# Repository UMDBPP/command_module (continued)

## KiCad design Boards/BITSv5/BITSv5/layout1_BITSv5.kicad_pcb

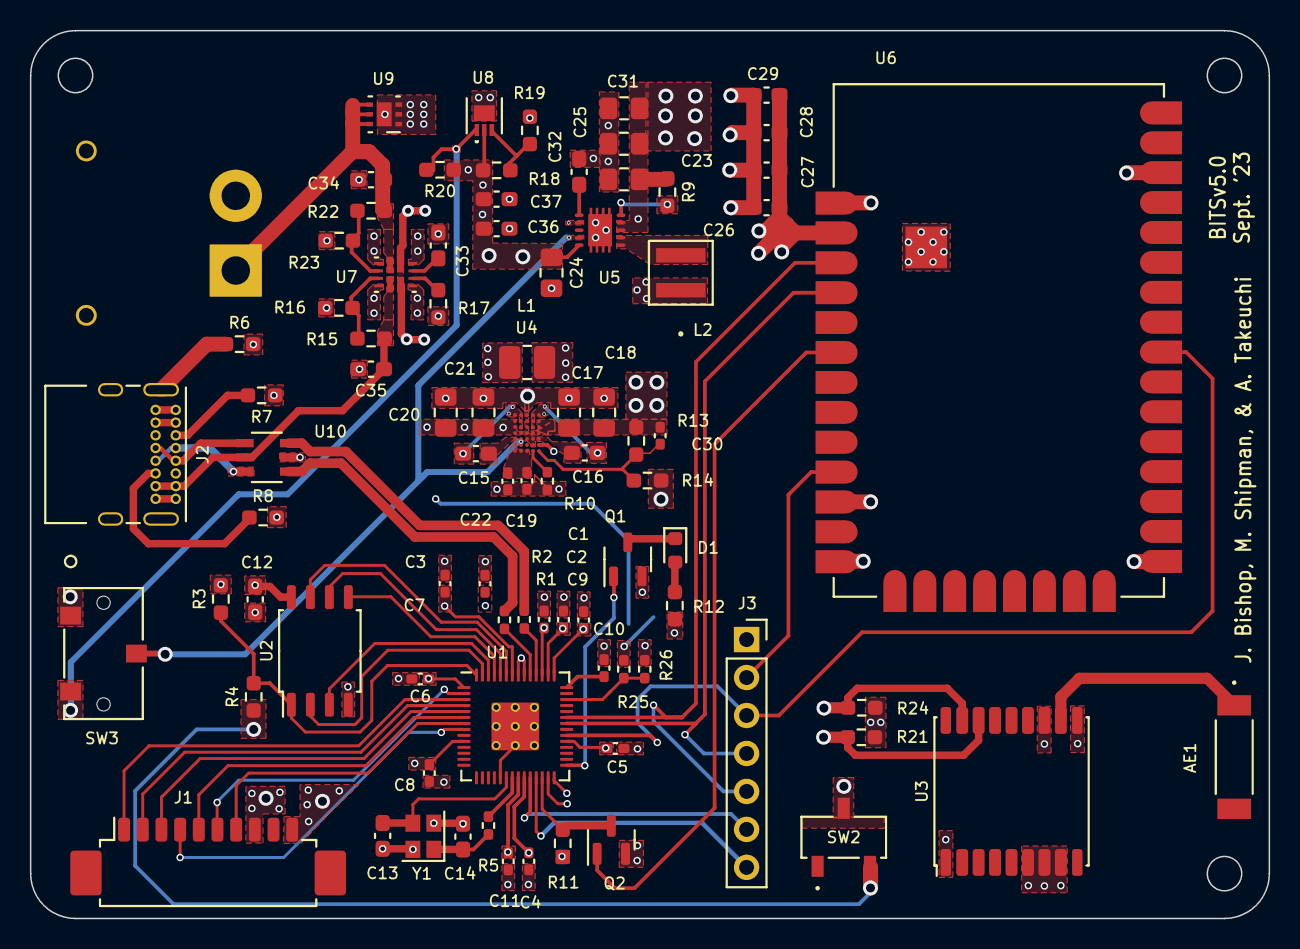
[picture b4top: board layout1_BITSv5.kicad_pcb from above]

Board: 4 copper layers, 82.9 x 59.4 mm, 86 parts (1 on the bottom side), 65 nets.

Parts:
AE1: Antenna; ANT_1575AT_JOT-M
BT1: 1S1P LiPo; AMASS_XT30PW-M_1x02_P2.50mm_Horizontal
C1, C2: 1uF; C_0402_1005Metric_Pad0.74x0.62mm_HandSolder
C3, C4, C5, C6, C7, C8, C9, C10, C11: 100nF; C_0402_1005Metric_Pad0.74x0.62mm_HandSolder
C12, C28: 100nF; C_0603_1608Metric_Pad1.08x0.95mm_HandSolder
C13, C14: 10pF; C_0603_1608Metric_Pad1.08x0.95mm_HandSolder
C15, C16: 220nF; C_0603_1608Metric_Pad1.08x0.95mm_HandSolder
C17, C18, C23, C24, C25, C31: 22uF; C_0805_2012Metric_Pad1.18x1.45mm_HandSolder
C19: 470nF; C_0402_1005Metric_Pad0.74x0.62mm_HandSolder
C20, C21: 10uF; C_0805_2012Metric_Pad1.18x1.45mm_HandSolder
C22: 2.2uF; C_0402_1005Metric_Pad0.74x0.62mm_HandSolder
C26: 8.2pF; C_0603_1608Metric_Pad1.08x0.95mm_HandSolder
C27: 47pF; C_0603_1608Metric_Pad1.08x0.95mm_HandSolder
C29, C34, C35: 10uF; C_0603_1608Metric_Pad1.08x0.95mm_HandSolder
C30: 10pF; C_0402_1005Metric_Pad0.74x0.62mm_HandSolder
C32, C33: 10nF; C_0603_1608Metric_Pad1.08x0.95mm_HandSolder
C36, C37: 1uF; C_0603_1608Metric_Pad1.08x0.95mm_HandSolder
D1: LED; LED_0603_1608Metric
J1: Conn_01x10_Pin; Molex_PicoBlade_53261-1071_1x10-1MP_P1.25mm_Horizontal
J2: USB_C_Receptacle_USB2.0; USB_C_Receptacle_GCT_USB4085
J3: Conn_01x07; PinSocket_1x07_P2.54mm_Vertical
L1: 1uH; L_1008_2520Metric_Pad1.43x2.20mm_HandSolder
L2: 1uH; IND_XAL4020_4X4_COC-M
Q1: Q_NMOS_GSD; SOT-23-3
Q2: Q_PMOS_GSD; SOT-23
R1, R2: 27Ω; R_0402_1005Metric_Pad0.72x0.64mm_HandSolder
R3, R11, R21, R24: 10K; R_0603_1608Metric_Pad0.98x0.95mm_HandSolder
R4: 1K; R_0603_1608Metric_Pad0.98x0.95mm_HandSolder
R5: 1K; R_0402_1005Metric_Pad0.72x0.64mm_HandSolder
R6, R9: 1M; R_0603_1608Metric_Pad0.98x0.95mm_HandSolder
R7, R8: 5.1K; R_0603_1608Metric_Pad0.98x0.95mm_HandSolder
R10: 48.7K; R_0402_1005Metric_Pad0.72x0.64mm_HandSolder
R12: 470; R_0603_1608Metric_Pad0.98x0.95mm_HandSolder
R13: 178K; R_0603_1608Metric_Pad0.98x0.95mm_HandSolder
R14: 20K; R_0603_1608Metric_Pad0.98x0.95mm_HandSolder
R15, R22: 23.7K; R_0603_1608Metric_Pad0.98x0.95mm_HandSolder
R16, R23: 5K; R_0603_1608Metric_Pad0.98x0.95mm_HandSolder
R17: 51.1K; R_0603_1608Metric_Pad0.98x0.95mm_HandSolder
R18: 1.05M; R_0603_1608Metric_Pad0.98x0.95mm_HandSolder
R19: 154K; R_0603_1608Metric_Pad0.98x0.95mm_HandSolder
R20: 510K; R_0603_1608Metric_Pad0.98x0.95mm_HandSolder
R25: 15K; R_0402_1005Metric_Pad0.72x0.64mm_HandSolder
R26: 5K; R_0402_1005Metric_Pad0.72x0.64mm_HandSolder
SW2: CAS-120TB_NDC-M
SW3: SLIDE; CL-SB-12B-01_NDC
U1: MCU_RaspberryPi_RP2040_RP2040; RP2040-QFN-56
U2: W25Q128JVS; SOIC-8_5.23x5.23mm_P1.27mm
U3: MAX-M10S; ublox_MAX
U4: MAX77857; MAX77857-35WLP
U5: TPS61232DRCR; TPS61232
U6: XBee_SMT; XCVR_XBP9X-DMUS-001
U7: TPS2121RUXR; TPS2121
U8: LT6703CDC-3; DFN-3_DC_LIT
U9: TVS1800DRVR; TVS1800
U10: USBLC6-2SC6; SOT23-6L_STM-M
Y1: 12MHz; Crystal_SMD_2520-4Pin_2.5x2.0mm

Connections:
+1V1: C1.1, C3.1, C4.1, U1.23 (DVDD), U1.45 (VREG_VOUT), U1.50 (DVDD)
+3V3: C2.1, C5.1, C6.1, C7.1, C8.1, C9.1, C10.1, C11.1, C12.1, C17.1, C18.1, C26.1, C27.1, C28.1, C29.1, C30.1, R3.2, R11.1, R12.1, R13.1, R21.1, R24.1, U1.1 (IOVDD), U1.10 (IOVDD), U1.22 (IOVDD), U1.33 (IOVDD), U1.42 (IOVDD), U1.43 (ADC_AVDD), U1.44 (VREG_IN), U1.48 (USB_VDD), U1.49 (IOVDD), U2.8 (VCC), U3.6 (V_BCKP), U3.7 (VCC_IO), U3.8 (VCC), U4.D4 (OUT), U4.E4 (OUT), U4.E5 (OUT), U4.E6 (OUT), U6.2 (VCC)
+5V: C23.1, C25.1, C31.1, J1.8, R9.1, U5.3 (VOUT), U5.4 (VOUT), U5.7 (FB)
+BATT: BT1.1 (+), C34.1, R22.1, R25.1, U7.2 (IN2), U9.4 (IN), U9.5 (IN), U9.6 (IN)
/GPS_SCL: R24.2, U1.28 (GPIO17), U3.17 (SCL)
/GPS_SDA: R21.2, U1.27 (GPIO16), U3.16 (SDA)
/IRIDIUM_CTS: J1.2, U1.4 (GPIO2)
/IRIDIUM_NETAV: J1.4, U1.8 (GPIO6)
/IRIDIUM_ON/OFF: J1.7, U1.7 (GPIO5)
/IRIDIUM_RING: J1.5, U1.6 (GPIO4)
/IRIDIUM_RTS: J1.3, U1.5 (GPIO3)
/IRIDIUM_RXD: J1.1, U1.3 (GPIO1)
/IRIDIUM_TXD: J1.6, U1.2 (GPIO0)
/LED: Q1.1 (G), U1.29 (GPIO18)
/LVC_CUTOFF: SW3.2 (B), U4.B2 (EN), U4.B3 (EN), U5.9 (EN)
/QSPI_SCLK: U1.52 (QSPI_SCLK), U2.6 (CLK)
/QSPI_SD0: U1.53 (QSPI_SD0), U2.5 (DI(IO0))
/QSPI_SD1: U1.55 (QSPI_SD1), U2.2 (DO(IO1))
/QSPI_SD2: U1.54 (QSPI_SD2), U2.3 (IO2)
/QSPI_SD3: U1.51 (QSPI_SD3), U2.7 (IO3)
/QSPI_SS: R3.1, R4.2, U1.56 (QSPI_SS), U2.1 (~CS)
/RP_SWCLK: J3.6, U1.24 (SWCLK)
/RP_SWD: J3.7, U1.25 (SWD)
/USB_D+: R2.1, U10.1
/USB_D-: R1.1, U10.3
/VBAT: R25.2, R26.2, U1.40 (GPIO28_ADC2)
/XBEE_DIN: J3.4, U1.36 (GPIO24), U6.4 (DIO14/DIN/~CONFIG)
/XBEE_DOUT: J3.5, U1.37 (GPIO25), U6.3 (DIO13/DOUT)
/XBEE_DTR: J3.2, U6.10 (DIO8/~DTR~{/SLEEP_RQ)
/XBEE_RESET: Q2.1 (G), U6.6 (~RESET)
/XBEE_RTS: J3.3, U1.34 (GPIO22), U6.29 (DIO6/~RTS)
/XIN: C13.2, U1.20 (XIN), Y1.3
/XOUT: R5.2, U1.21 (XOUT)
GND: BT1.2 (-), C1.2, C2.2, C3.2, C4.2, C5.2, C6.2, C7.2, C8.2, C9.2, C10.2, C11.2, C12.2, C13.1, C14.1, C17.2, C18.2, C19.2, C20.2, C21.2, C22.2, C23.2, C24.2, C25.2, C26.2, C27.2, C28.2, C29.2, C31.2, C32.2, C33.2, C34.2, C35.2, C36.2, C37.2, J1.10, J2.A1 (GND), J2.A12 (GND), J2.B1 (GND), J2.B12 (GND), J3.1, Q1.2 (S), Q2.2 (S), R6.2, R7.1, R8.2, R10.2, R14.2, R16.2, R17.2, R19.2, R23.2, R26.1, SW2.3 (C), SW3.1 (A), U1.19 (TESTEN), U1.57 (GND), U2.4 (GND), U3.1 (GND), U3.10 (GND), U3.12 (GND), U4.C3 (PGND), U4.C4 (PGND), U4.C5 (PGND), U4.C6 (PGND), U4.C7 (PGND), U4.D2 (PGND), U4.D3 (PGND), U4.E2 (AGND), U5.11 (GND), U6.1 (GND), U6.11 (GND), U6.13 (GND), U6.22 (GND), U6.35 (GND), U6.38 (GND), U7.3 (CP2), U7.6 (PR1), U7.9 (ST), U7.12 (GND), U8.4 (V-), U9.1 (GND), U9.2 (GND), U9.3 (GND), U9.7 (PAD), U10.2, Y1.2, Y1.4
unnamed: AE1.1 (A), U3.11 (RF_IN)
unnamed: C14.2, R5.1, Y1.1
unnamed: C15.2, L1.1, U4.A7 (LX1), U4.B5 (LX1), U4.B6 (LX1), U4.B7 (LX1)
unnamed: C16.1, L1.2, U4.D5 (LX2), U4.D6 (LX2), U4.D7 (LX2), U4.E7 (LX2)
unnamed: D1.2 (A), R12.2
unnamed: D1.1 (K), Q1.3 (D)
unnamed: J2.A5 (CC1), R7.2
unnamed: J2.B5 (CC2), R8.1
unnamed: J2.A6 (D+), J2.B6 (D+), U10.6
unnamed: J2.A7 (D-), J2.B7 (D-), U10.4
unnamed: J2.S1 (SHIELD), R6.1
unnamed: L2.2, U5.1 (SW), U5.2 (SW)
unnamed: Q2.3 (D), R11.2, U1.26 (RUN)
unnamed: R4.1, SW2.2 (B)
unnamed: R20.2, SW3.3 (C), U8.1 (OUT)
unnamed: R1.2, U1.46 (USB_DM)
unnamed: R2.2, U1.47 (USB_DP)
unnamed: C15.1, U4.A3 (BST1)
unnamed: C16.2, U4.E3 (BST2)
unnamed: C30.2, R13.2, R14.1, U4.E1 (FB)
unnamed: C19.1, C22.1, U4.A1 (SCL), U4.A2 (VIO), U4.B1 (SDA), U4.C1 (VL)
unnamed: R10.1, U4.D1 (SEL)
unnamed: R9.2, U5.5 (PG)
unnamed: C32.1, U5.6 (SS)
unnamed: R17.1, U7.10 (ILM)
unnamed: R15.2, R16.1, U7.5 (OV1)
unnamed: R22.2, R23.1, U7.4 (OV2)
unnamed: C33.1, U7.11 (SS)
unnamed: R18.2, R19.1, U8.3 (IN+)
VBUS: C35.1, J2.A4 (VBUS), J2.A9 (VBUS), J2.B4 (VBUS), J2.B9 (VBUS), R15.1, U7.7 (IN1), U10.5
VCC: C20.1, C21.1, C24.1, C36.1, C37.1, L2.1, R18.1, R20.1, U4.A4 (IN), U4.A5 (IN), U4.A6 (IN), U4.B4 (IN), U5.10 (VIN), U7.1 (OUT), U7.8 (OUT), U8.2 (V+)

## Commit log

2020-01-08 Initial commit with boards
2020-01-09 Routed cell tracker board with power reg
2020-01-18 Cell tracker V3 routed
2020-01-19 Cleaned up the BITS schematic
2020-01-19 cleaned up cell schematic
2020-01-20 Removing 3v3 line, fixing the MOSFET I broke
2020-01-20 Cell Mosfet swap
2020-01-20 General board parts placement for BITS
2020-01-21 Dump of CAD files
2020-01-21 reverted bits schematic back to my last commit"
2020-01-21 Revert "reverted bits schematic back to my last commit""
    This reverts commit d8380e26c9c134d67ee78542be9b2ca2b8e420f0.
2020-01-21 Better fidelity cad
2020-01-21 Add cmdLibs lib
2020-01-21 Maybe fixing supply 1
2020-01-21 v7 Compatible file upload
2020-01-21 Integrate the BITS XBee
2020-01-21 Pushing the compatible version
2020-01-21 Updated the inductor and mosfet in cell schematic
2020-01-21 Adding connector to lib
2020-01-22 routed bits board
2020-01-22 Created an alternate board
2020-01-22 bits board try 2
2020-01-23 put connector on cell board, plus lots of cad work
2020-01-24 a whole lot of finshed nonsense
2020-02-04 All of the changes with CAD and electronics since switching to the microclasp connectors
2020-02-05 fixes and design review slides
2020-02-16 Updated boards
2020-05-13 Reorganizing files for new boards
2020-05-13 Fixing Errors, ditching coincell
2020-05-16 Fixing BITS brd
2020-05-19 Bunches of CAD, but I don't like CAD
2020-05-29 Box Passthroughs, fixing Iridium Board
2020-06-15 not much
2020-06-15 Adding Gitignore for s#h and b#d
2020-06-15 Changing antenna conf
2020-06-15 Putting all the code into this repo
2020-06-15 modding GS for choppy
2020-06-19 updating resistors for correct cutoff
2020-06-26 Code+nearly completed boards
2020-07-03 Moved libs, adding isolator
2020-07-04 More stuff, close, not done
2020-07-05 Finishing touches for Cell3.2
2020-07-06 Finalizing BITS v3.2
2020-07-12 Final board export/cam, code libraries fld
2020-07-13 Handling R values
2020-07-14 minor R val changes, STEP generation
2020-07-26 API testing/cellv3.1trigger software failREP
2020-07-26 Added board step files to CAD fld
2020-07-27 more liteAPRS debugging
2020-07-29 BITS3v1 flight code, liteAPRS code
2020-08-01 CellCode
2020-08-02 jtXBee updates
2020-08-02 Include active jtXBee files
2020-08-03 celltracker sms_rx done, memredux
2020-08-07 NS92 prelim code FRZ
2020-08-17 Cell Assem Fin
2020-08-20 Cell Board appears to work
2020-08-26 New GPS procedures
2020-08-29 NewCell fixes
2020-08-30 Cell3.2 working, freeze
2020-08-30 NS93_code_FRZ
2020-09-03 Debugging Cell3v2
2020-09-15 buffer simplification
2020-10-09 New Testing File, v3.2 test
2020-10-16 New folder for test code, with in house gps lib
2020-10-16 setting up gps lib test
2021-01-09 Trying some new hardware configs
2021-01-11 changing some colors and taking screenshots
2021-01-15 a commit
2021-01-20 plate mounting bolt holes
2021-01-25 Adding a copy of the AdafruitRFM95 board for ref
2021-01-25 LightAPRS switching reg/LVC updates
2021-01-25 routed lightAPRS LVC
2021-01-26 Finished new LightAPRS LVC/REG
2021-02-01 Cutting down the adafruit rfm board
2021-02-20 box fixes
2021-03-14 Box changes
2021-03-15 New_lid
2021-03-18 Adding in Bitsv2 board CAD
2021-03-18 re-order/confirm LVC fix
2021-03-31 Plate mounting holes
2021-04-03 new_reg work
    LMR50410XF reg design to cover and possibly replace LMR16020 for <1A command things
2021-07-06 plate for v2 bits brd
2021-07-08 lightAPRS code fix
2021-08-08 re-arrange some file structure, init boxv4
2021-08-08 Box v4 draft
2021-08-19 New reg board
    LM20242
2021-09-16 routed board...?
2021-09-26 improved spacing between rockblock and bits board on plate
2021-10-03 BITSv4
    omg I need a clock so bad
2021-10-04 LED reposition
2021-10-09 connector move
2021-10-13 TextMove
2021-12-11 new choppy
2022-01-02 code for second xbee trigger using arduino pro mini
2022-01-12 file changes
2022-04-16 TestedBoard
    omg_it_works
2022-04-17 BoardUpdate
2022-04-19 Clone v3.2 to v4
2022-04-19 Comments, lots of Comments
2022-04-21 Completed Commenting Primary File
2022-04-21 Enough changes a test should happen
2022-04-21 Added voltage reporting
2022-04-22 Unbroke the code again
2022-04-22 AvgAscentRate added
2022-04-25 FixingErrors
    snprintf unhappy, modifying that
2022-04-25 Another Fix
2023-05-26 new ghoul xbee
2023-07-31 bits v5 board begins
2023-07-31 BITSv5 updates
2023-08-11 BITSv5 sch almost done
2023-08-13 more bits updates
2023-08-18 bits v5 board nearly done
2023-08-19 several hundred bits v5 errors later
2023-08-20 bits v5 board feedback added
2023-08-20 no more 5 am commits
2023-08-23 BITSv5 layout changes
2023-08-25 small update to BITSv5 for review
2023-08-26 BITSv5 board done
2023-08-26 xbee joint board begins
2023-08-28 xbee joint board updates
2023-08-30 xbee joint and bits updates
2023-09-04 most up to date bits and xbee joint
2023-09-04 added button to BITS5
2023-09-04 working on xbee joint
2023-09-05 xbee joint layout almost complete
2023-09-05 BITSv5 USB change
2023-09-05 BITSv5 added additional Xbee connector
2023-10-09 ns122 updates to do
2023-10-19 bits v5 w/ dorji radio
2023-10-19 dorji joint?
2023-10-23 ordered new joint and bits
2023-11-03 added kicad-lib submodule
2023-11-05 messing with RP2040 code
2023-11-05 more testing code
2023-11-05 submodule stuff
2023-11-05 submodule fixes
2023-11-05 more submodule fixes
2023-11-05 starting to refactor radio library
2023-11-06 added blink to BITSv5 test code
2023-11-06 additional reference code
2023-11-07 more BITSv5 code experimentation
2023-11-08 radio test code that compiles?
2023-11-08 trying serial input too
2023-11-09 xbee joint test code
2023-11-09 last ugh?
2023-11-10 xbee joint radio test code
2023-11-10 this radio is annoying me
2023-11-10 tx continuous wave works
2023-11-10 xbee joint +25 dBm continuous wave
2023-11-10 more radio code
2023-11-10 receive IRQ works now
2023-11-11 transmit and receive on BITS and (Not)Xbee Joint, packets are recognized (valid preamble detected) but a header error is thrown on receive (LoRa header CRC error)
2023-11-14 more xbee joint code
2023-11-14 yeppers
2023-11-16 minor (Not)Xbee Joint refactor, deleted LittleFS from (Not)Xbee Joint too
2023-11-27 README typo that was there for god knows how long
2023-11-28 minor (not)xbee joint code change
2023-11-29 more (not)xbee joint futzing, still doesn't work :(
2023-12-08 cleaned up some radio code
2023-12-09 the radios were working like an hour ago
2023-12-09 RADIO WORKS
2023-12-09 saved some radio test proof and code
2023-12-09 more clean up
2023-12-10 started big sx1262 lib refactor
2023-12-10 init SX1262 lib and hopefully fix crusty submodule issue
2023-12-10 using sx1262 lib in BITSv5 now, also more submodule decrustification
2023-12-10 added multiple build targets for BITSv5
2023-12-10 (Not)Xbee Joint automation
2023-12-11 (not)xbee joint <-> bits lora comms work, just not ping pong for some reason
2023-12-11 automation fixes
2023-12-11 automation fixes again
2023-12-11 deleted kicad-lib submodule
2023-12-11 re-added kicad-lib submodule tracking main
2023-12-11 trying to fix these submodules
2023-12-11 these submodules omg
2023-12-11 geez
2023-12-11 BITSv5 software README
2023-12-16 updated release tags for BITSv5 and (Not)Xbee Joint to v0.0.1
2023-12-22 first pass at MS5607 library
2023-12-22 created MS5607 library submodule
2023-12-22 ok now BITSv5 compiles with MS5607 lib
2024-01-18 added some new libraries (rp2040-config, rp2040-console, std-cmd)
2024-01-24 started adding rp2040-console support to (Not)Xbee Joint test code
2024-01-26 adding console support to (Not)Xbee Joint test code
2024-01-26 I think console/radio test code ready
2024-01-26 compiles with config library
2024-01-26 send and lstn commands work
2024-01-27 moved BITS header and created BITS gps-test
2024-01-27 updated rp2040 config and console
2024-01-27 clean up changes
2024-01-27 changed BITsv5 Test auto build to only trigger on pushes to BITSv5 test code
2024-01-27 testing new BITSv5 auto build
2024-01-31 starting BITSv5.1 hardware rev
2024-01-31 changed BITSv5 antennas to ufl, added TIMEPULSE and EXTINT GPIOs, and exposed GPIO UART over header
2024-02-01 BITSv5.1 ready for review
2024-02-01 nvm I want BITSv5 to have a chip antenna
2024-02-01 finished GPS chip antenna, removed SOICbite for test points because couldn't find space
2024-02-01 clean up
2024-02-02 BITSv5.1 ready for order, Gerbers generated
2024-02-02 new art footprints
2024-02-02 updated rp2040-console
2024-02-04 BITSv5.1 STEP file and dimensions
2024-02-08 added logs from v5 GPS lock attempts
2024-02-11 BITS radio no long draws almost 100 mA idle
2024-02-11 updated drf1262 lib
2024-02-11 syncing BITSv5 and (Not)Xbee Joint boards
2024-02-13 added interrupt support to DRF1262 lib and (Not)Xbee Joint code
2024-02-13 sync drf1262 lib
2024-02-14 refined the interrupt implementation for the drf1262 library, there are rough edges but it's fine
2024-02-14 tried to see if new txen fix for the radio would make the GPS magically work but it didn't :(
2024-02-14 synced drf1262 library
2024-02-17 starting power changes for BITSv5.2
2024-02-18 BITSv5.2 new power system laid out
2024-02-19 ordered BITSv5.2
2024-02-25 changes for ns-124
2024-02-25 potentially flyable ns-124 changes
2024-03-02 ns124 aftermath changes
2024-03-02 BITSv5.2 changes
2024-03-02 libraries updates
2024-03-02 rp2040 libraries sync
2024-03-02 fixed FRAM library include for (Not)Xbee Joint
2024-03-03 fixed Models:Drawings
2024-03-06 BITS improvements, logging test and radio irq
2024-03-06 (Not)Xbee Joint updates
2024-03-07 FRAM logging in progress, addressing hopefully finally works properly now
2024-03-07 logging and dumping from FRAM working
2024-03-08 BITS changes
2024-03-09 radio-test code for BITSv5.2 works now, RX and TX
2024-03-10 BITS radio working again
2024-03-13 Copied over some structs from libnmea and outlined how parsing could operate
2024-03-13 Added a little more to parsing
2024-03-13 Copied several more functions
2024-03-15 Finished first draft
2024-03-15 radio test updates
2024-03-22 updates for NS-125, very hasty/messy changes
2024-03-22 first pass at iridium driver for BITSv5
2024-03-22 update libraries
2024-03-22 minor changes
2024-03-26 iridium driver updates, SBDIX parsing broken but basics confirmed working
2024-04-19 new header files for config and code sharing
2024-04-19 made Not_XbeeJoint autobuild only run on relevant changes
2024-07-19 actually going to try writing the actual fligh code now
2025-02-14 saving state before minimizing this test project
2025-02-24 minimal GPS example code, need to test
2025-02-24 minimal radio example code, need to test
2025-02-24 iridium test code, need to test, not full minimal example yet
2025-02-27 tested basic functionality, def some issues to work out, also added channel activity detection which needs to be tested
2025-04-09 first attempts at BITSv5 arduino code because it's time I got my shit together, also featuring modified arduino-cli docker container for building
2025-04-09 trying to commit docker container source
2025-04-11 refactor in progress
2025-04-21 minor GPS parsing change for BITSv4, TinyGPS -> TinyGPSPlus
2025-11-21 new build with new GHOUL Xbee Address 0x4256DDBC
2025-11-21 updated Xbee address
2025-11-21 BITSv4 reproducible build support with arduino-cli
2025-11-22 maybe actually real GPS parse updates this time? I really don't know what happened and I'm going a little crazy lowkey
2025-11-26 actual GPS parse update
2025-11-27 update gitignore to ignore files in build directories
2025-11-27 update gitignore to ignore all DS_Store
2025-11-27 remove DS_Store
2025-11-27 add github action to build BITSv4 code
2025-11-27 update action to apply to branch
2025-11-27 update action so I can test it with PR
2025-11-27 change arduino-cli install directory bc idk what I'm doing
2025-11-27 update action
2025-11-27 added docs on auto build system
2025-11-27 Create BITSv4 Build System (#24)
    * BITSv4 reproducible build support with arduino-cli
    * update gitignore to ignore files in build directories
    * update gitignore to ignore all DS_Store
    * remove DS_Store
    * add github action to build BITSv4 code
    * update action to apply to branch
